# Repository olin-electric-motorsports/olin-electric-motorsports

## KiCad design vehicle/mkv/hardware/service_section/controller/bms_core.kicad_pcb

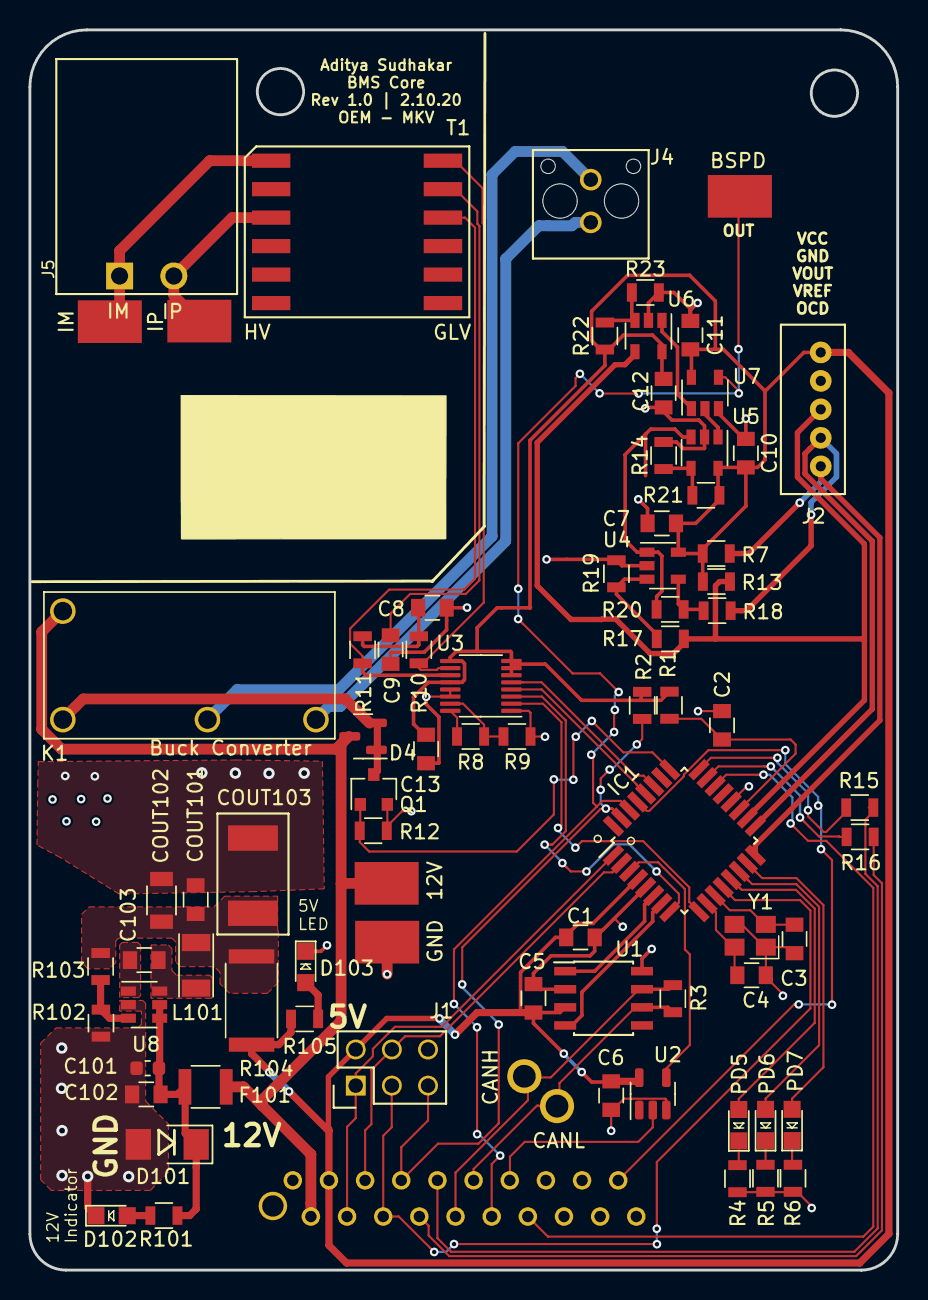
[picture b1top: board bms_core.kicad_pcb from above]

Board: 2 copper layers, 61.0 x 87.1 mm, 81 parts (1 on the bottom side), 62 nets.

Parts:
12V: Test_Point_SMD
BSPD: Test_Point_SMD
C1, C5, C6, C7, C10, C11, C12, C13, C102, C103: C_0.1uF; C_0805_OEM
C2: C_100pF; C_0805_OEM
C3, C4: C_30pF; C_0805_OEM
C8, C9: C_10nF; C_0805_OEM
C101: C_2.2uF; C_0603_1608Metric
CANH: TP; tp_1.6mm
CANL: TP; tp_1.6mm
COUT101: C_47uF; C_0805_OEM
COUT102: C_22uF; C_1206_OEM
COUT103: C_33uF; Fuse_1812
D4: BAS40-00; SOT-23
D101: D_Zener_18V; DO-214AA
D102, D103: LED_0805; LED_0805_OEM
F101: 500mA; Fuse_1210
GND: Test_Point_SMD
IC1: ATMEGA16M1; TQFP-32_7x7mm_Pitch0.8mm
IM: Test_Point_SMD
IP: Test_Point_SMD
J1: CONN_02X03; Pin_Header_Straight_2x03
J2: B5B-PH-K-S
J3: MM_F_VT_20; micromatch_female_vert_20
J4: MicroFit_V_2
J5: isoSPI-Cutout; iso_spi_cutout
K1: G5Q-1A4-DC12; Relay_SPST_OMRON-G5Q-1A4_OEM
L101: L_100uH; L_100uH_OEM
PD5, PD6, PD7: LED_0805; LED_0805_OEM
Q1: SSM3K333R; SOT-23F
R1: R_100; R_0805_OEM
R2, R7, R12, R13, R17, R18, R19, R20, R22: R_10K; R_0805_OEM
R3, R4, R5, R6, R15, R16, R105: R_200; R_0805_OEM
R8, R9, R23, R101: R_1K; R_0805_OEM
R10, R11: R_60.4; R_0805_OEM
R14: R_1K_0.1; R_0805_OEM
R21: R_14.3K; R_0805_OEM
R102: R_25K; R_0805_OEM
R103: R_100K; R_0805_OEM
R104: R_0_2512; R_2512_OEM
T1: T_LAN_SM91501ALE
U1: MCP2561-E_SN; SOIC-8_3.9x4.9mm_Pitch1.27mm_OEM
U2: SN74LVC1G17; SOT-23-5
U3: LTC6820HMS; MSOP-16_3x4mm_P0.5mm
U4, U5, U6: MCP6001; SOT-23-5_OEM
U7: SN74LVC1G32; SOT-23-5_OEM
U8: TPS560430YF; SOT-23-6_OEM
Y1: Crystal_SMD; Crystal_SMD_FA238

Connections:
+12V: 12V.1, D4.3, F101.1, J3.2, K1.5
/BMS_SENSE: IC1.22, J3.14
/BSPD_CURRENT: BSPD.1, IC1.30, J3.12, U7.4
/CANH: CANH.1, J3.10, R3.1, U1.7
/CANL: CANL.1, J3.11, R3.2, U1.6
/CHARGE_ENABLE1: IC1.29, J3.19
/CS_iso: IC1.27, U3.5
/FAN_PWM: J3.13, U2.2
/FAN_PWM_RAW: IC1.3, U2.4
/IM: IM.1, J5.1, T1.1
/IP: IP.1, J5.2, T1.3
/MISO: IC1.1, J1.1, J3.4
/MISO_iso: IC1.8, U3.3
/MOSI: IC1.2, J1.4, J3.5
/MOSI_iso: IC1.9, U3.2
/PROG_1: IC1.13, PD5.2
/PROG_2: IC1.14, PD6.2
/PROG_3: IC1.15, PD7.2
/RELAY_DRIVE: IC1.25, Q1.1, R12.2
/RESET: IC1.31, J1.5, J3.7, R2.2
/RJ45_LED1: J3.8, R16.1
/RJ45_LED2: J3.9, R15.1
/RXCAN: IC1.7, U1.4
/SCK: IC1.12, J1.3, J3.6
/SCK_iso: IC1.28, U3.4
/SHDN_IN(MAIN_PACK->BMS): J4.1, K1.3
/SHDN_OUT(BMS->IMD): J4.2, K1.2
/TXCAN: IC1.6, U1.1
/VOUT: IC1.18, J2.3, R13.1, R17.1, U6.4
/VREF: IC1.17, J2.4, R18.1
/~OCD: IC1.16, J2.5, R7.2
GND: C1.2, C2.2, C3.2, C4.2, C5.2, C6.1, C7.2, C8.2, C9.2, C10.2, C11.2, C12.2, C13.2, C101.2, C102.2, COUT101.2, COUT102.2, COUT103.2, D101.2, D102.1, D103.1, GND.1, IC1.5, IC1.20, J1.6, J2.2, J3.1, J3.15, J3.16, J3.17, J3.18, J3.20, J3.21, Q1.2, R4.2, R5.2, R6.2, R9.2, R12.1, R14.2, R19.1, R23.2, R102.2, U1.2, U1.8, U2.3, U3.1, U3.13, U3.14, U4.2, U5.2, U6.2, U7.3, U8.2, Y1.2, Y1.4
unnamed: C2.1, IC1.19, R1.2
unnamed: C3.1, IC1.11, Y1.1
unnamed: C4.1, IC1.10, Y1.3
unnamed: C8.1, R10.2, R11.1
unnamed: C9.1, T1.11
unnamed: C101.1, C102.1, D101.1, F101.2, R101.1, U8.4, U8.5
unnamed: C103.1, L101.1, U8.6
unnamed: C103.2, U8.1
unnamed: COUT101.1, COUT102.1, COUT103.1, L101.2, R103.2, R104.2
unnamed: D4.1, D4.2, K1.1, Q1.3
unnamed: D102.2, R101.2
unnamed: D103.2, R105.2
unnamed: IC1.23, R16.2
unnamed: IC1.24, R15.2
unnamed: PD5.1, R4.1
unnamed: PD6.1, R5.1
unnamed: PD7.1, R6.1
unnamed: R8.1, U3.16
unnamed: R8.2, R9.1, U3.15
unnamed: R10.1, T1.12, U3.10
unnamed: R11.2, T1.10, U3.11
unnamed: R14.1, R21.1, U5.4
unnamed: R17.2, R19.2, U4.3
unnamed: R18.2, R20.1, U4.4
unnamed: R20.2, U4.1, U5.3
unnamed: R22.2, R23.1, U6.3
unnamed: R102.1, R103.1, U8.3
unnamed: U5.1, U7.2
unnamed: U6.1, U7.1
VCC: C1.1, C5.1, C6.2, C7.1, C10.1, C11.1, C12.1, C13.1, IC1.4, J1.2, J2.1, J3.3, R1.1, R2.1, R7.1, R13.2, R21.2, R22.1, R104.1, R105.1, U1.3, U2.5, U3.6, U3.7, U3.8, U3.9, U3.12, U4.5, U5.5, U6.5, U7.5

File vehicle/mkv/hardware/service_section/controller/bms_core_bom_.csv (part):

Component,Description,Part,References,Value,Footprint,Quantity Per PCB,Datasheet,Package,MPN,MFN,PurchasingLink
1,"Capacitor, 0.1uF, 50V, 5%, 0805",C_0.1uF,C1 C5 C6 C7 C10 C102 C105,C_0.1uF,C_0805_OEM,7,http://datasheets.avx.com/X7RDielectric.pdf,Value,478-3352-1-ND,Digi-Key DK,https://www.digikey.com/products/en?keywords=478-3352-1-ND
2,"Capacitor, 100pF, 50V, 5%, 0805",C_100pF,C2,C_100pF,C_0805_OEM,1,https://content.kemet.com/datasheets/KEM_C1003_C0G_SMD.pdf,Value,399-1122-1-ND,Digi-Key,https://www.digikey.com/product-detail/en/kemet/C0805C101J5G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
3,"Capacitor, 10nF 50V X7R 0805",C_10nF,C8 C9,C_10nF,C_0805_OEM,2,http://www.samsungsem.com/kr/support/product-search/mlcc/__i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,,1276-1015-1-ND,DK,https://www.digikey.com/product-detail/en/samsung-electro-me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
4,"Capacitor, 1uF, 25V, 10%, 0805",C_1uF,C104,C_1uF,C_0805_OEM,1,http://datasheets.avx.com/X7RDielectric.pdf,Value,478-10487-1-ND,Digi-Key,https://www.digikey.com/product-detail/en/avx-corporation/08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
5,"Capacitor, 22uF, 16V, 20%, 1206",C_22uF,C101,C_22uF,C_1206_OEM,1,http://www.samsungsem.com/kr/support/product-search/mlcc/__i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,Value,1276-2725-1-ND,Digi-Key,https://www.digikey.com/products/en?keywords=1276-2725-1-ND
6,"Capacitor, 30pF, 50V, 5%, 0805",C_30pF,C3 C4,C_30pF,C_0805_OEM,2,https://media.digikey.com/pdf/Data%20Sheets/Samsung%20PDFs/C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,Value,1276-1130-1-ND,Digi-Key,https://www.digikey.com/product-detail/en/samsung-electro-me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
7,"Capacitor, 47uF, 6.3V, 20%, 0805",C_47uF,C103,C_47uF,C_0805_OEM,1,http://www.yuden.co.jp/productdata/catalog/en/mlcc_all_e.pdf,Value,587-4280-1-ND,Digi-Key,https://www.digikey.com/product-detail/en/taiyo-yuden/JMK212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
8,"Schottky Diode, 40V, 120mA, SOT23",BAS40-00,D4,BAS40-00,SOT-23,1,https://assets.nexperia.com/documents/data-sheet/BAS40_1PSXX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,,1727-4234-1-ND,DK,https://www.digikey.com/product-detail/en/nexperia-usa-inc/B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
9,"Diode, Zener, 18V, 5W, 5%",D_Zener_18V,D101,D_Zener_18V,DO-214AA,1,http://www.mccsemi.com/up_pdf/SMBJ5338B-SMBJ5388B(SMB).pdf,DO-214AA (SMB),SMBJ5355B-TPMSCT-ND,Digi-Key,https://www.digikey.com/products/en?keywords=SMBJ5355B-TPMSCT-ND
10,"LED, Green, 2.2V, 20mA, 0805",LED_0805,D1 D2 D3 D102 D103,LED_0805,LED_0805_OEM,5,http://www.osram-os.com/Graphics/XPic9/00078860_0.pdf,Value,475-1410-1-ND,DK Digi-Key,https://www.digikey.com/products/en?keywords=475-1410-1-ND
11,"Fuse, PTC, 500mA, 16V, 1210",F_500mA_16V,F101,500mA,Fuse_1210,1,https://belfuse.com/resources/CircuitProtection/datasheets/0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,Value,507-1786-1-ND,Digi-Key,https://www.digikey.com/product-detail/en/bel-fuse-inc/0ZCH0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
12,"Microcontroller, 8-bit, 1KB RAM, 16KB Flash",ATMEGA16M1,IC1,ATMEGA16M1,TQFP-32_7x7mm_Pitch0.8mm,1,http://www.atmel.com/Images/Atmel-8209-8-bit%20AVR%20ATmega1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,Value,ATMEGA16M1-AU-ND,Digi-Key,https://www.digikey.com/product-detail/en/atmel/ATMEGA16M1-A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
13,"Connector Header Through Hole 5 position 0.079"" (2.00mm)",B5B-PH-K-S,J2,B5B-PH-K-S,B5B-PH-K-S,1,http://www.jst-mfg.com/product/pdf/eng/ePH.pdf,,455-1707-ND,DK,https://www.digikey.com/product-detail/en/jst-sales-america-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
14,"Connector header through hole 2x3 0.100"" (2.54mm)",CONN_02X03,J1,CONN_02X03,Pin_Header_Straight_2x03,1,http://portal.fciconnect.com/Comergent//fci/drawing/67996.pdf,Value,609-3234-ND,Digi-Key,https://www.digikey.com/product-detail/en/amphenol-fci/67997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
15,Micro-MaTch connector 14 pin female vertical,MM_F_VT_14,J5,MM_F_VT_14,micromatch_female_vert_14,1,http://www.te.com/commerce/DocumentDelivery/DDEController?Ac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,,1-338068-4,TE,http://www.te.com/global-en/product-1-338068-4.html
16,"Micro-Fit Connector, Right Angle 2 circuit",MicroFit_RA_R_2,J4,MicroFit_RA_R_2,MicroFit_RA_2,1,https://www.molex.com/pdm_docs/sd/436500201_sd.pdf,,WM1865-ND,DK,https://www.digikey.com/product-detail/en/molex/0436500201/W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
17,Nano-Fit connector 2 pin right angle,NanoFit_2,J3,NanoFit_2,NanoFit_Molex_1x02x2.50mm_Angled_OEM,1,https://www.molex.com/pdm_docs/sd/1053131102_sd.pdf,,WM14972-ND,DK,https://www.digikey.com/products/en/connectors-interconnects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
18,"Relay, SPST-NO, Switch 10A/30V, Coil 40mA/5V",G5Q-1A4-DC5-5V,K1,G5Q-1A4-DC5-5V,Relay_SPST_OMRON-G5Q-1A4_OEM,1,http://omronfs.omron.com/en_US/ecb/products/pdf/en-g5q.pdf,,Z3632-ND,DK,https://www.digikey.com/product-detail/en/omron-electronics-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
19,"Inductor, 4.7uH, 4.4A, 25mOhm, 20%",L_4.7uH,L101,L_4.7uH,4.7uH_Inductor_OEM,1,https://product.tdk.com/info/en/documents/wdcatalog/withdraw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,Value,445-6583-1-ND,Digi-Key,https://www.digikey.com/product-detail/en/tdk-corporation/VL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
20,"MOSFET, N-channel, 30V, 6A",SSM3K333R,Q1,SSM3K333R,SOT-23F,1,https://drive.google.com/drive/folders/0B-V-iZf33Y4GNzhDQTJZanJRbVk,,SSM3K333RLFCT-ND,DK,https://www.digikey.com/product-detail/en/toshiba-semiconduc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
21,"Resistor, 0 ohm jumper, 3W, 2512",R_0_2512,R105,R_0_2512,R_2512_OEM,1,http://www.te.com/commerce/DocumentDelivery/DDEController?Ac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,,A121322CT-ND,DK,https://www.digikey.com/products/en?keywords=A121322CT-ND
22,"Resistor, 100, 0.25W, 1%, 0805",R_100,R1,R_100,R_0805_OEM,1,https://www.seielect.com/Catalog/SEI-rncp.pdf,Value,RNCP0805FTD100RCT-ND,Digi-Key,https://www.digikey.com/products/en?keywords=RNCP0805FTD100RCT-ND
23,"Resistor, 10K, 0.25W, 1%, 0805",R_10K,R2 R7 R12 R102 R103,R_10K,R_0805_OEM,5,http://www.bourns.com/data/global/pdfs/CRS.pdf,,CRS0805-FX-1002ELFCT-ND,DK,https://www.digikey.com/products/en?keywords=CRS0805-FX-1002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
24,"Resistor, 17.4K, 0.125W, 0.1%, 0805",R_17.4K_0.1,R13,R_17.4K_0.1,R_0805_OEM,1,https://industrial.panasonic.com/cdbs/www-data/pdf/RDM0000/A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,,P17.4KDACT-ND,DK,https://www.digikey.com/product-detail/en/panasonic-electron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
25,"Resistor, 1K, 0.25W, 1%, 0805",R_1K,R9 R101,R_1K,R_0805_OEM,2,https://www.seielect.com/Catalog/SEI-rncp.pdf,,RNCP0805FTD1K00CT-ND,DK,https://www.digikey.com/products/en?keywords=RNCP0805FTD1K00CT-ND
26,"Resistor, 1K, 0.125W, 0.1%, 0805",R_1K_0.1,R14,R_1K_0.1,R_0805_OEM,1,https://industrial.panasonic.com/cdbs/www-data/pdf/RDM0000/A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,,P1.0KDACT-ND,DK,https://www.digikey.com/product-detail/en/panasonic-electron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
27,"Resistor, 200, 0.125W, 5%, 0805",R_200,R3 R4 R5 R6 R15 R16 R106,R_200,R_0805_OEM,7,https://www.seielect.com/Catalog/SEI-RMCF_RMCP.pdf,Value,RMCF0805JT200RCT-ND,Digi-Key DK,https://www.digikey.com/products/en?keywords=RMCF0805JT200RCT-ND
28,"Resistor, 3.01K, 0.125W, 1%, 0805",R_3.01K,R8,R_3.01K,R_0805_OEM,1,http://www.yageo.com.tw/exep/pages/download/literatures/PYu-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,,311-3.01KCRCT-ND,DK,https://www.digikey.com/products/en?keywords=311-3.01KCRCT-ND
29,"Resistor, 54.9, 0.125W, 1%, 0805",R_54.9K,R104,R_54.9K,R_0805_OEM,1,https://industrial.panasonic.com/cdbs/www-data/pdf/RDA0000/A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,,311-54.9KCRCT-ND,DK,https://www.digikey.com/product-detail/en/yageo/RC0805FR-075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
30,"Resistor, 60.4, 0.1%, 0.125W, 0805",R_60.4,R10 R11,R_60.4,R_0805_OEM,2,https://industrial.panasonic.com/cdbs/www-data/pdf/RDM0000/A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,,P60.4DACT-ND,DK,https://www.digikey.com/product-detail/en/panasonic-electron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
31,Transformer LAN 10/100 base-T,T_LAN_7490100111A,T1,T_LAN_7490100111A,T_LAN_7490100111A,1,https://katalog.we-online.de/pbs/datasheet/7490100111A.pdf,,732-5711-1-ND,DK,https://www.digikey.com/product-detail/en/wurth-electronics-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
32,isoSPI Isolated Communications Interface,LTC6820HMS,U3,LTC6820HMS,MSOP-16_3x4mm_P0.5mm,1,https://www.analog.com/media/en/technical-documentation/data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,,LTC6820HMS#TRPBFCT-ND,DK,https://www.digikey.com/product-detail/en/linear-technology-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
33,"High speed CAN transceiver, 1Mb/s",MCP2561-E_SN,U1,MCP2561-E_SN,SOIC-8_3.9x4.9mm_Pitch1.27mm_OEM,1,http://www.microchip.com/mymicrochip/filehandler.aspx?ddocna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,,MCP2561-E/SN-ND,DK,https://www.digikey.com/products/en?keywords=mcp2561-e%2Fsn
34,"Op-amp, general purpose",MCP6001,U4 U5,MCP6001,SOT-23-5_OEM,2,http://ww1.microchip.com/downloads/en/DeviceDoc/21733j.pdf,,MCP6001T-I/OTCT-ND,DK,https://www.digikey.com/product-detail/en/microchip-technolo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
35,Single schmitt-trigger buffer,SN74LVC1G17,U2,SN74LVC1G17,SOT-23-5,1,http://www.ti.com/lit/ds/symlink/sn74lvc1g17.pdf,,296-11933-1-ND,DK,https://www.digikey.com/product-detail/en/texas-instruments/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

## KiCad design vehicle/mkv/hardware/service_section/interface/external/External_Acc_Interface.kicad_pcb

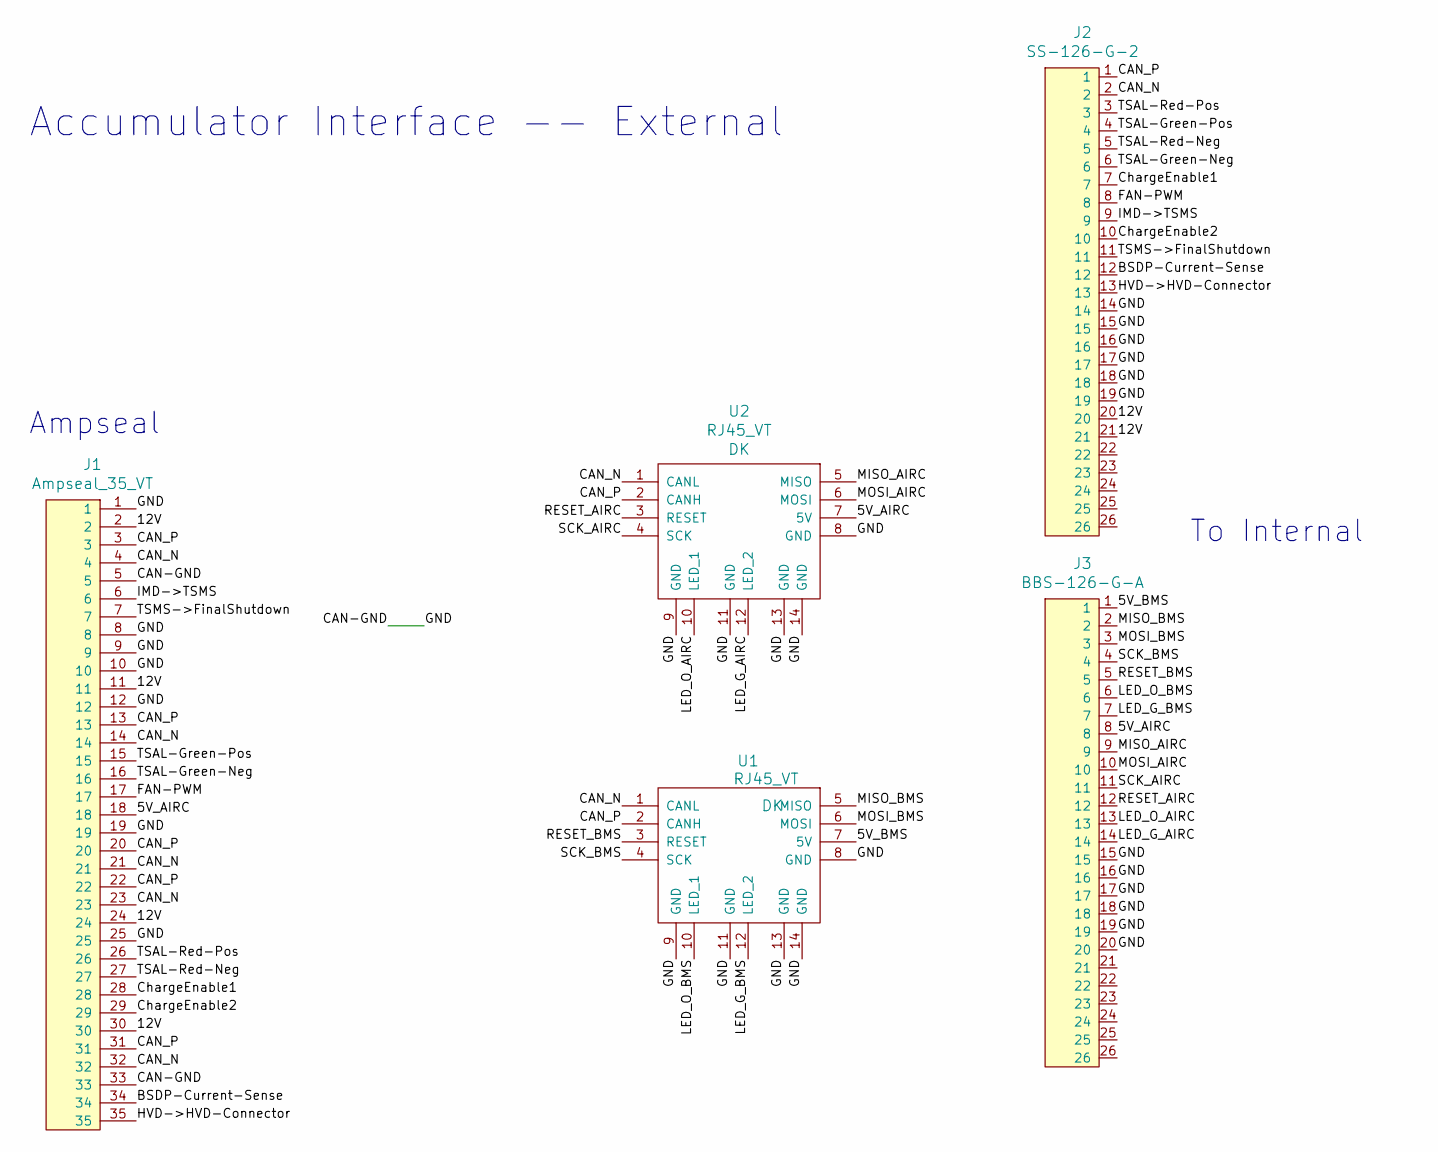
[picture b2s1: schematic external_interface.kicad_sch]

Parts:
J1: Ampseal_35_VT; Ampseal_35; MPN 1-776231-1
J2: SS-126-G-2; 26pos_screwsocket_.1in; MPN SS-126-G-2
J3: BBS-126-G-A; 26pos_screwsocket_.1in; MPN BBS-126-G-A
U1, U2: RJ45_VT; RJ45-Vertical; MPN MRJ-5481-01-ND

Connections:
/5V_AIRC: J1.18, J3.8, U2.7 (5V)
/5V_BMS: J3.1, U1.7 (5V)
/12V: J1.2, J1.11, J1.24, J1.30, J2.20, J2.21
/BSDP-Current-Sense: J1.34, J2.12
/CAN-GND: J1.1, J1.5, J1.8, J1.9, J1.10, J1.12, J1.19, J1.25, J1.33, J2.14, J2.15, J2.16, J2.17, J2.18, J2.19, J3.15, J3.16, J3.17, J3.18, J3.19, J3.20, U1.8 (GND), U1.9 (GND), U1.11 (GND), U1.13 (GND), U1.14 (GND), U2.8 (GND), U2.9 (GND), U2.11 (GND), U2.13 (GND), U2.14 (GND)
/CAN_N: J1.4, J1.14, J1.21, J1.23, J1.32, J2.2, U1.1 (CANL), U2.1 (CANL)
/CAN_P: J1.3, J1.13, J1.20, J1.22, J1.31, J2.1, U1.2 (CANH), U2.2 (CANH)
/ChargeEnable1: J1.28, J2.7
/ChargeEnable2: J1.29, J2.10
/FAN-PWM: J1.17, J2.8
/HVD->HVD-Connector: J1.35, J2.13
/IMD->TSMS: J1.6, J2.9
/LED_G_AIRC: J3.14, U2.12 (LED_2)
/LED_G_BMS: J3.7, U1.12 (LED_2)
/LED_O_AIRC: J3.13, U2.10 (LED_1)
/LED_O_BMS: J3.6, U1.10 (LED_1)
/MISO_AIRC: J3.9, U2.5 (MISO)
/MISO_BMS: J3.2, U1.5 (MISO)
/MOSI_AIRC: J3.10, U2.6 (MOSI)
/MOSI_BMS: J3.3, U1.6 (MOSI)
/RESET_AIRC: J3.12, U2.3 (RESET)
/RESET_BMS: J3.5, U1.3 (RESET)
/SCK_AIRC: J3.11, U2.4 (SCK)
/SCK_BMS: J3.4, U1.4 (SCK)
/TSAL-Green-Neg: J1.16, J2.6
/TSAL-Green-Pos: J1.15, J2.4
/TSAL-Red-Neg: J1.27, J2.5
/TSAL-Red-Pos: J1.26, J2.3
/TSMS->FinalShutdown: J1.7, J2.11

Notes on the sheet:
To Internal
Accumulator Interface -- External
Ampseal

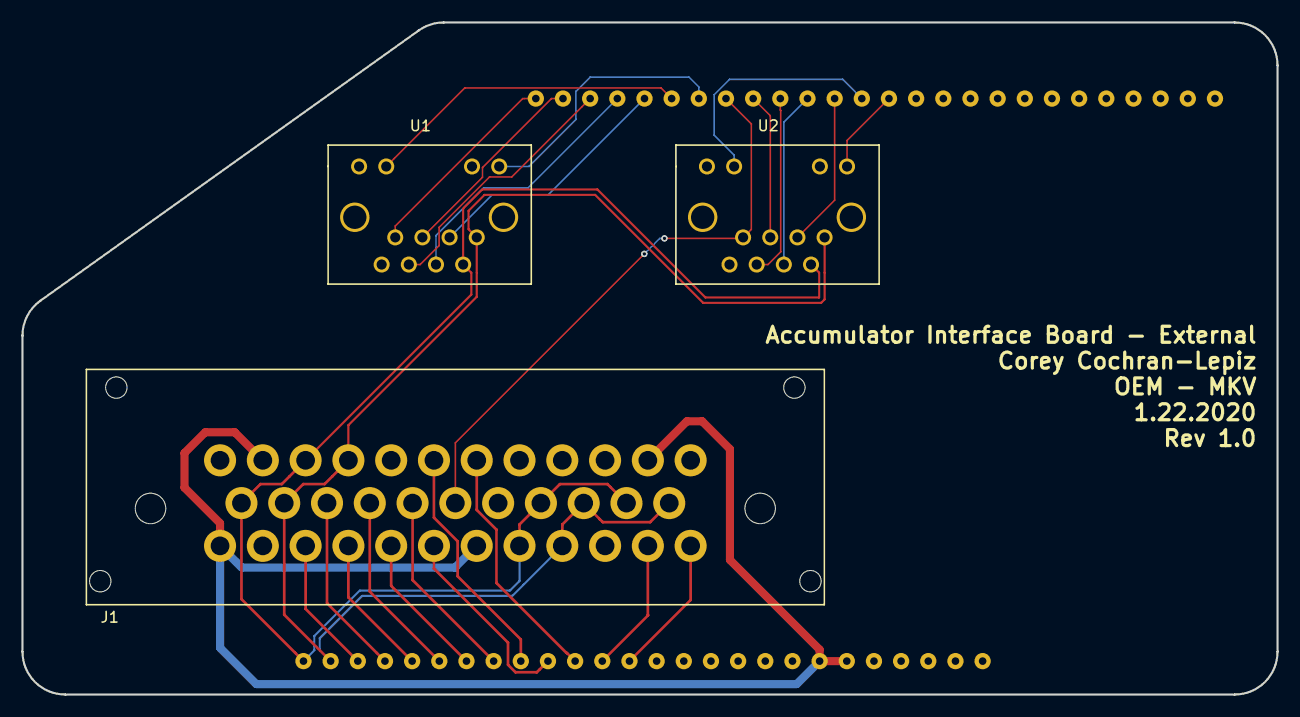
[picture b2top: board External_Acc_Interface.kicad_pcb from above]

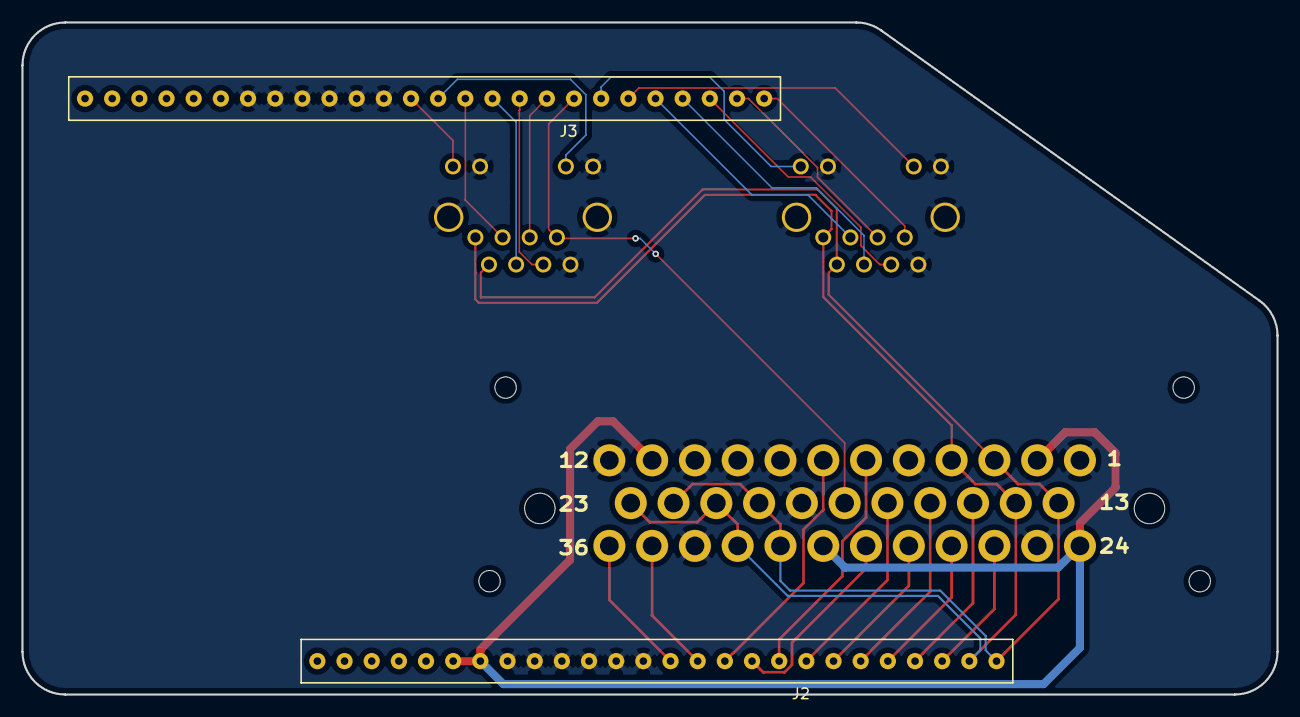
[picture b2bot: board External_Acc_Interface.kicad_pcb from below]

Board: 2 copper layers, 117.4 x 62.8 mm, 5 parts (2 on the bottom side), 29 nets.

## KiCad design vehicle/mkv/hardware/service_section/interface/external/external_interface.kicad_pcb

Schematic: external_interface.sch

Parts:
J1: Ampseal_35_VT; Ampseal_35; MPN 1-776231-1
J2: SS-126-G-2; 26pos_screwsocket_.1in; MPN SS-126-G-2
J3: BBS-126-G-A; 26pos_screwsocket_.1in; MPN BBS-126-G-A
J4: UF_2_RA; Ultrafit_2_RA; MPN WM11825-ND
U1, U2: RJ45_VT; RJ45-Vertical; MPN MRJ-5481-01-ND

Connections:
/5V_AIRC: J3.20, U2.7 (5V)
/5V_BMS: J3.13, U1.7 (5V)
/12V: J1.10, J1.11, J1.21, J1.22, J2.20, J2.21
/BSDP-Current-Sense: J1.30, J2.12
/BSDP-Current-Trigger+: J1.34, J4.2
/CAN_EMETER_N: J1.33, J2.17
/CAN_EMETER_P: J1.32, J2.16
/CAN_N: J1.4, J1.7, J1.14, J2.2, U1.1 (CANL), U2.1 (CANL)
/CAN_P: J1.3, J1.6, J1.13, J2.1, U1.2 (CANH), U2.2 (CANH)
/ChargeEnable1: J1.28, J2.7
/ChargeEnable2: J1.29, J2.10
/CoolingBat1+: J1.24, J3.2, J3.4, J3.6
/CoolingBat1-: J1.2, J3.1, J3.3, J3.5
/CoolingBat2+: J1.25, J3.8, J3.10, J3.12
/CoolingBat2-: J1.1, J3.7, J3.9, J3.11
/FAN-PWM: J2.8
/HVD->HVD-Connector: J1.31, J2.13
/IMD->TSMS: J1.18, J2.9
/LED_G_AIRC: J3.26, U2.12 (LED_2)
/LED_G_BMS: J3.19, U1.12 (LED_2)
/LED_O_AIRC: J3.25, U2.10 (LED_1)
/LED_O_BMS: J3.18, U1.10 (LED_1)
/MISO_AIRC: J3.21, U2.5 (MISO)
/MISO_BMS: J3.14, U1.5 (MISO)
/MOSI_AIRC: J3.22, U2.6 (MOSI)
/MOSI_BMS: J3.15, U1.6 (MOSI)
/RESET_AIRC: J3.24, U2.3 (RESET)
/RESET_BMS: J3.17, U1.3 (RESET)
/SCK_AIRC: J3.23, U2.4 (SCK)
/SCK_BMS: J3.16, U1.4 (SCK)
/TSAL-Green-Neg: J1.16, J2.6
/TSAL-Green-Pos: J1.15, J2.4
/TSAL-Red-Neg: J1.27, J2.5
/TSAL-Red-Pos: J1.26, J2.3
/TSMS->FinalShutdown: J1.19, J2.11

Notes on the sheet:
Ampseal
To Internal
Accumulator Interface -- External
CoolingBat# is to funnel current. Each ampsel pin can take 17A Cooling bat will 'see' 24A so we give each a pin and load each at 12A

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
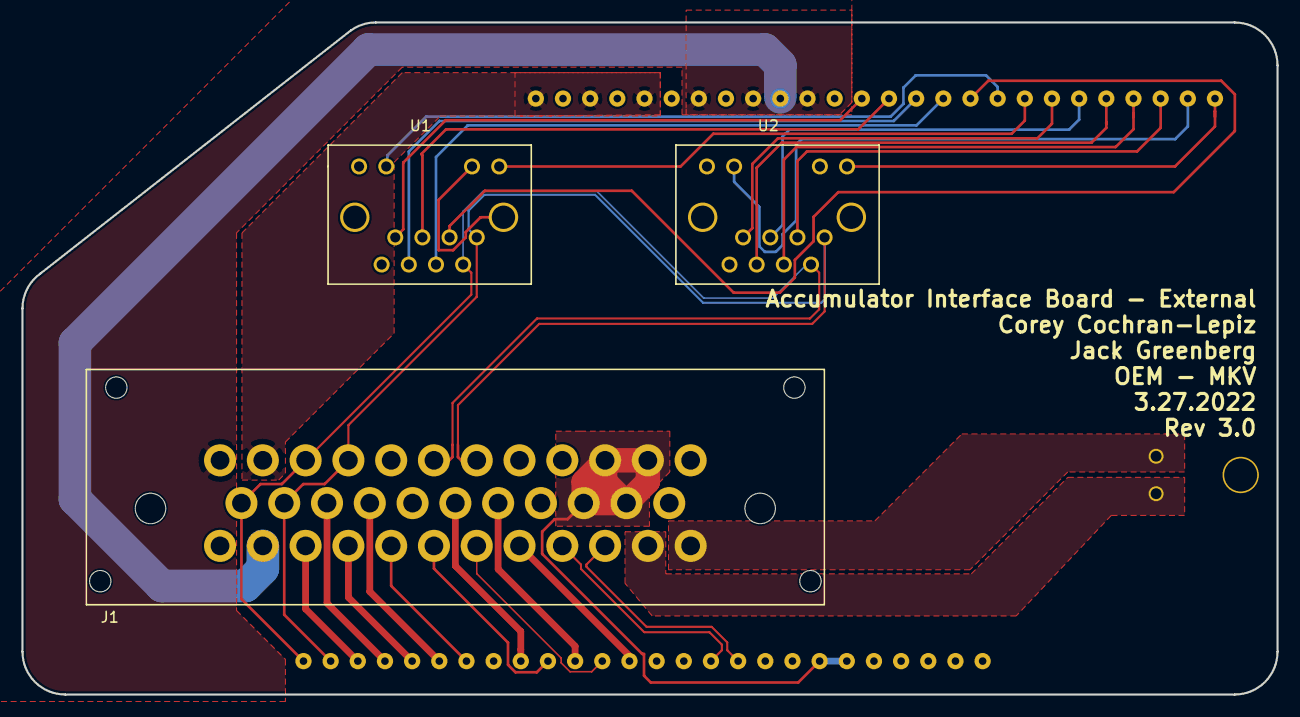
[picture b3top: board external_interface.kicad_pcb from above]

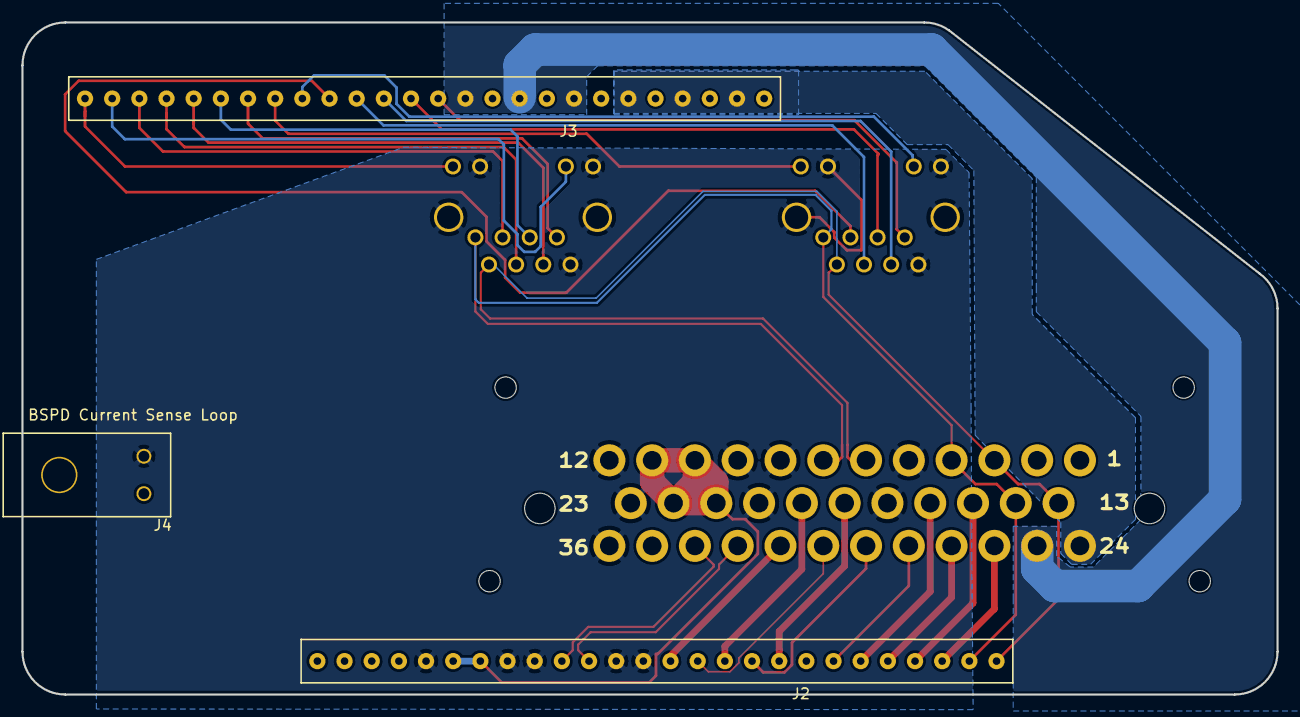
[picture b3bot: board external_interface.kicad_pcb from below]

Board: 2 copper layers, 117.4 x 62.8 mm, 6 parts (3 on the bottom side), 35 nets.

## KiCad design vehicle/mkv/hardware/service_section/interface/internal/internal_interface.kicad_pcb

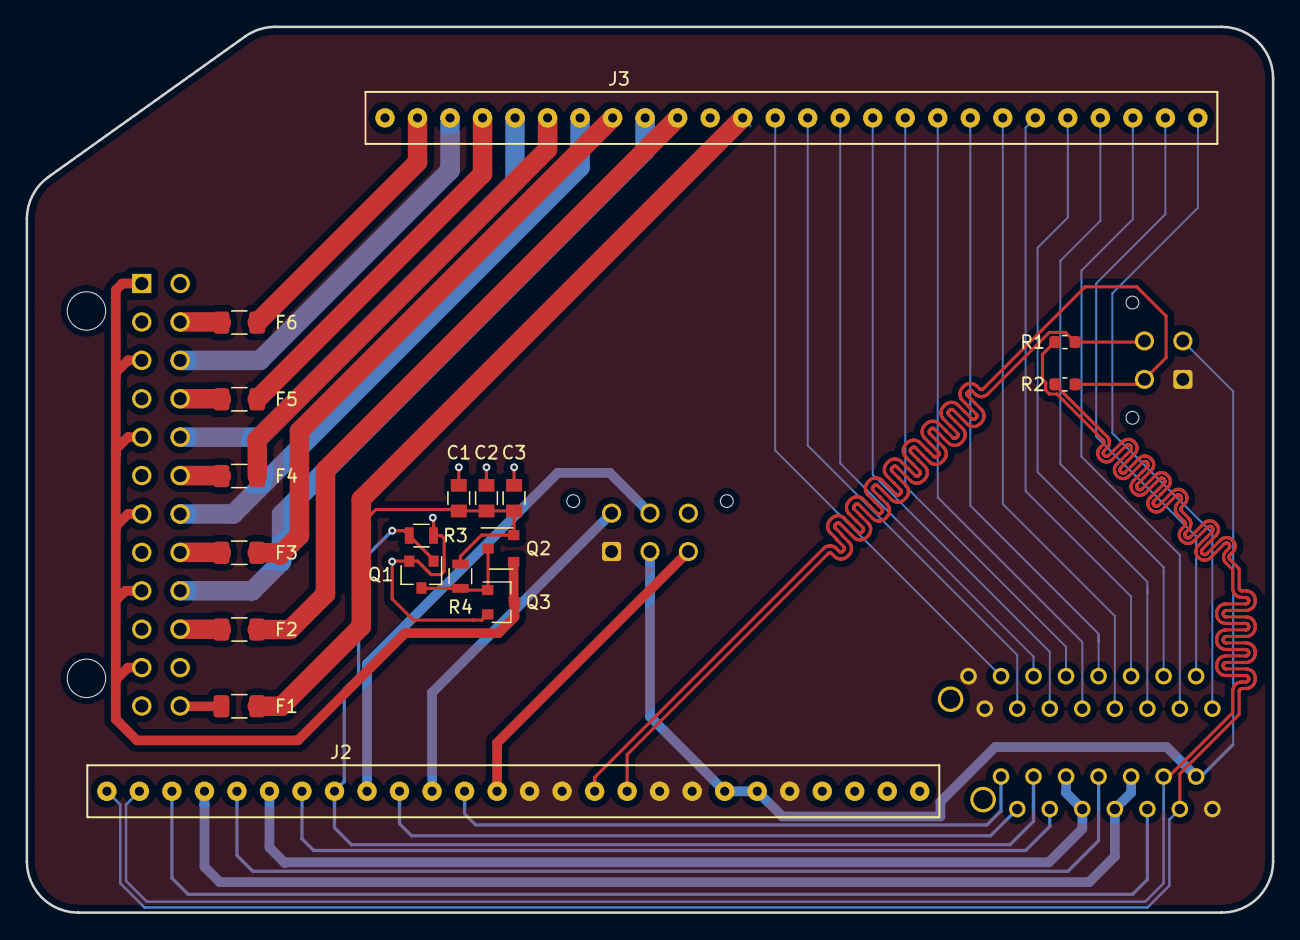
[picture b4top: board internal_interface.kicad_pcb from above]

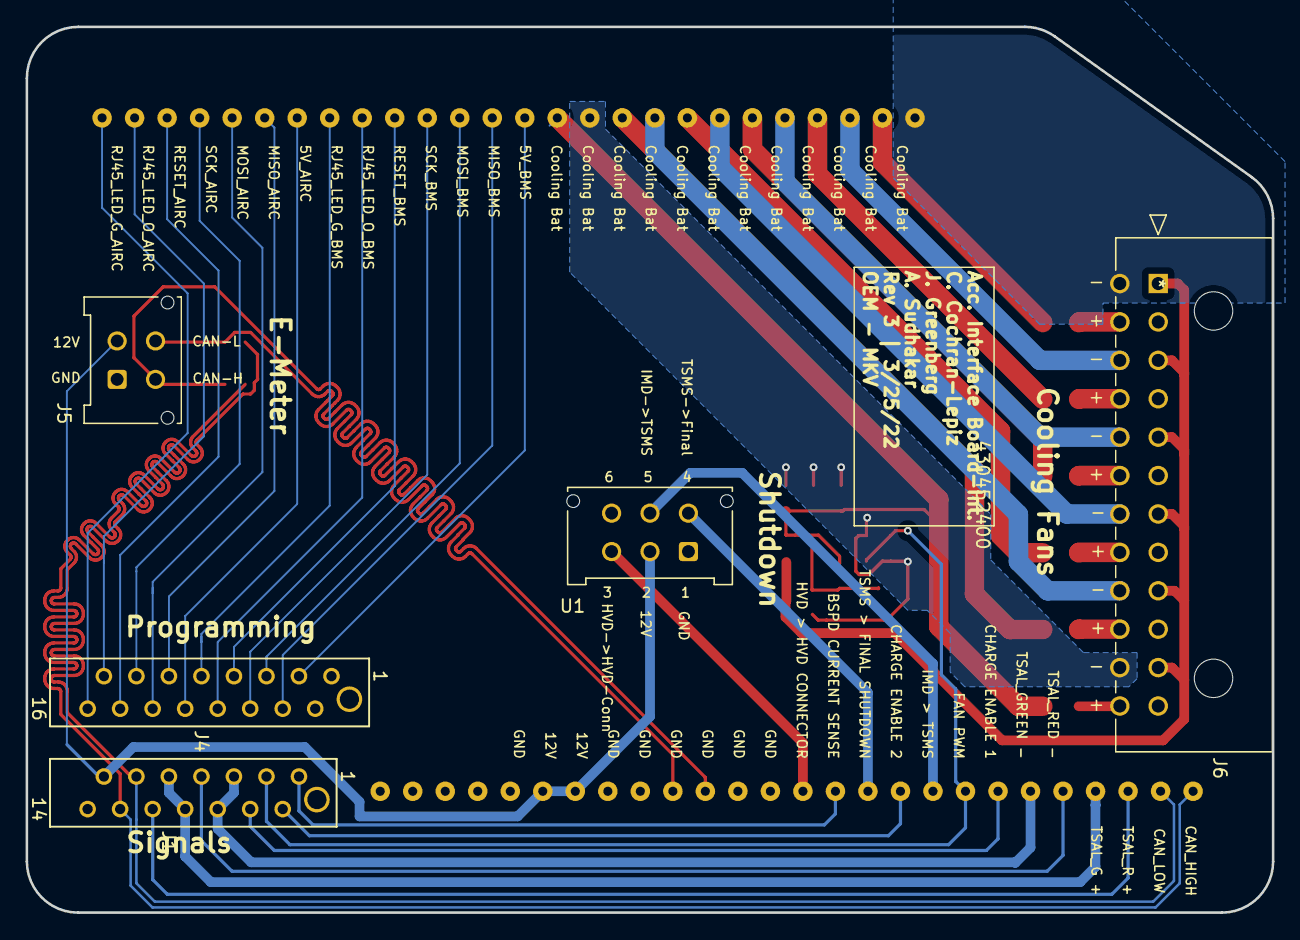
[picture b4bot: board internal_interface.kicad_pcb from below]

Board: 2 copper layers, 97.4 x 69.2 mm, 23 parts (5 on the bottom side), 51 nets.

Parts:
C1, C2, C3: C_10uF; C_0805_OEM
F1, F2, F3, F4, F5, F6: F_4A; Fuse_1206
J1: MM_F_VT_14; micromatch_female_vert_14
J2: SS-126-G-2; 26pos_screwsocket_.1in
J3: BBS-126-G-A; 26pos_screwsocket_.1in
J4: MM_F_VT_16; micromatch_female_vert_16
J5: MicroFit_VT_4
J6: MicroFit_24; Molex_Microfit3_Header_02x12_Straight_0444322401_OEM
Q1, Q3: SSM3K333R; SOT-23F
Q2: BSS308PE; SOT-23-3_OEM
R1, R2: R_0; R_0603_1608Metric
R3: R_10K; R_0805_OEM
R4: R_1K; R_0805_OEM
U1: MicroFit_VT_6

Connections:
/5V_AIRC: J3.20, J4.10
/5V_BMS: J3.13, J4.3
/12V: J1.13, J2.20, J2.21, J5.2, U1.2
/BSDP-Current-Sense: J1.1, J2.12
/CAN_EMETER_N: J2.17, J5.4, R1.1
/CAN_EMETER_P: J2.16, J5.3, R2.1
/CAN_N: J1.11, J2.2, R1.2
/CAN_P: J1.12, J2.1, R2.2
/ChargeEnable1: J1.4, J2.7
/ChargeEnable2: J1.2, J2.10
/CoolingBat1+: F6.1, J3.2
/CoolingBat1-: J3.1, J6.13
/CoolingBat2+: F5.1, J3.4
/CoolingBat2-: J3.3, J6.15
/CoolingBat3+: F4.1, J3.6
/CoolingBat3-: J3.5, J6.17
/CoolingBat4+: F3.1, J3.8
/CoolingBat4-: J3.7, J6.19
/CoolingBat5+: F2.1, J3.10
/CoolingBat5-: J3.9, J6.21
/CoolingBat6+: C1.1, C2.1, C3.1, F1.1, J3.12, Q2.3, R4.1
/CoolingBat6-: C1.2, C2.2, C3.2, J3.11, J6.23, Q1.2, Q3.2, R3.2
/FAN-PWM: J1.3, J2.8, Q1.1, R3.1
/HVD->HVD-Connector: J2.13, U1.3
/IMD->TSMS: J2.9, U1.5
/LED_G_AIRC: J3.26, J4.16
/LED_G_BMS: J3.19, J4.9
/LED_O_AIRC: J3.25, J4.15
/LED_O_BMS: J3.18, J4.8
/MISO_AIRC: J3.21, J4.11
/MISO_BMS: J3.14, J4.4
/MOSI_AIRC: J3.22, J4.12
/MOSI_BMS: J3.15, J4.5
/RESET_AIRC: J3.24, J4.14
/RESET_BMS: J3.17, J4.7
/SCK_AIRC: J3.23, J4.13
/SCK_BMS: J3.16, J4.6
/TSAL-Green-Neg: J1.5, J1.6, J2.6
/TSAL-Green-Pos: J1.8, J1.9, J2.4
/TSAL-Red-Neg: J1.7, J2.5
/TSAL-Red-Pos: J1.10, J2.3
/TSMS->FinalShutdown: J2.11, U1.4
/fanPWM: J6.1, J6.3, J6.5, J6.7, J6.9, J6.11, Q2.2, Q3.3
GND: J1.14, J2.14, J2.15, J2.18, J2.19, J2.22, J4.1, J4.2, J5.1, U1.1
unnamed: F1.2, J6.24
unnamed: F2.2, J6.22
unnamed: F3.2, J6.20
unnamed: F4.2, J6.18
unnamed: F5.2, J6.16
unnamed: F6.2, J6.14
unnamed: Q1.3, Q2.1, Q3.1, R4.2

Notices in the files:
parts and their libraries:
Copyright 2021 Accelerated Designs. All rights reserved.
